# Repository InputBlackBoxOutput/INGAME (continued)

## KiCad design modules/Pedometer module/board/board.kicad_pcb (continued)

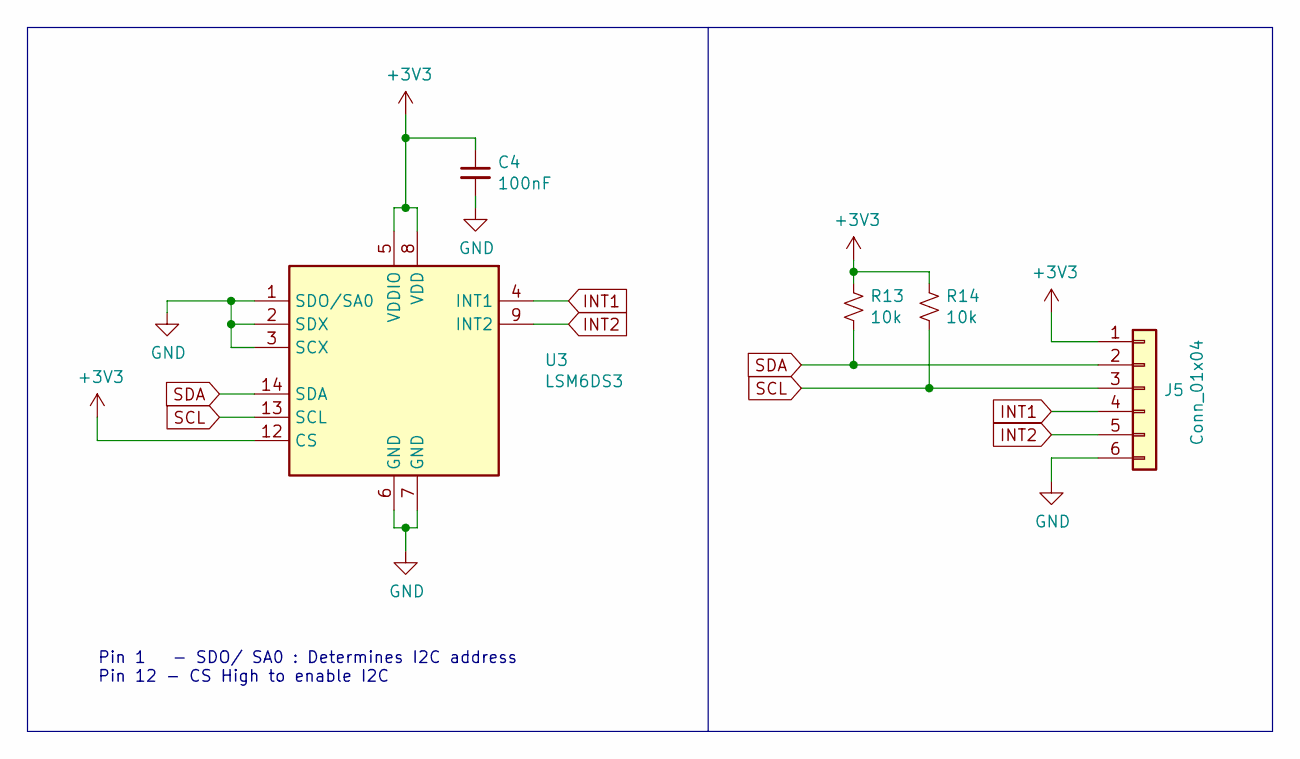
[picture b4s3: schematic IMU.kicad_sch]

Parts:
C4: 100nF; C_0603_1608Metric_Pad1.08x0.95mm_HandSolder
J5: Conn_01x04; SolderWire_1x06_P2.54mm
R13, R14: 10k; R_0603_1608Metric_Pad0.98x0.95mm_HandSolder
U3: LSM6DS3; LGA-14_3x2.5mm_P0.5mm_LayoutBorder3x4y

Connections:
GND: C4.2, J5.6, U3.1 (SDO/SA0), U3.2 (SDX), U3.3 (SCX), U3.6 (GND), U3.7 (GND); also elsewhere on the board
INT1: J5.4, U3.4 (INT1); also elsewhere on the board
INT2: J5.5, U3.9 (INT2); also elsewhere on the board
SCL: J5.3, R14.1, U3.13 (SCL); also elsewhere on the board
SDA: J5.2, R13.1, U3.14 (SDA); also elsewhere on the board

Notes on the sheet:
Pin 1 - SDO/ SA0 : Determines I2C address Pin 12 - CS High to enable I2C

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
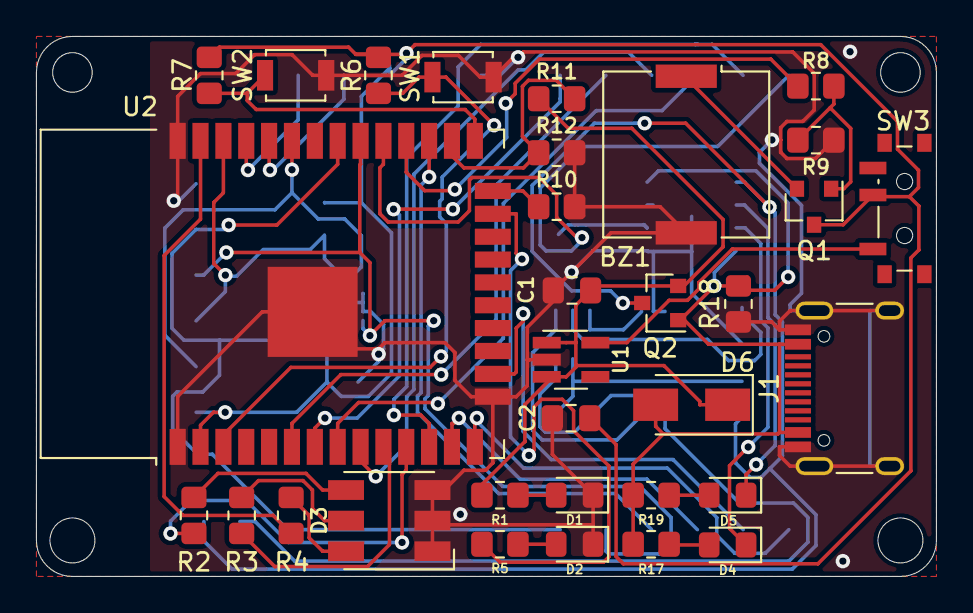
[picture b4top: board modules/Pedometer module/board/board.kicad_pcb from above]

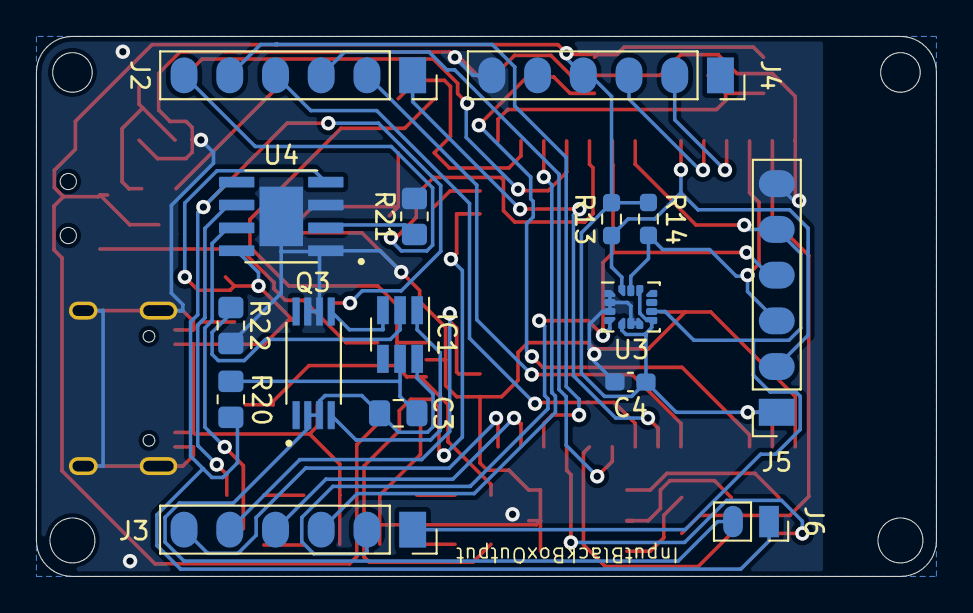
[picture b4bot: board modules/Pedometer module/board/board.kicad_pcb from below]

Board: 2 copper layers, 50.0 x 30.0 mm, 52 parts (16 on the bottom side), 48 nets.

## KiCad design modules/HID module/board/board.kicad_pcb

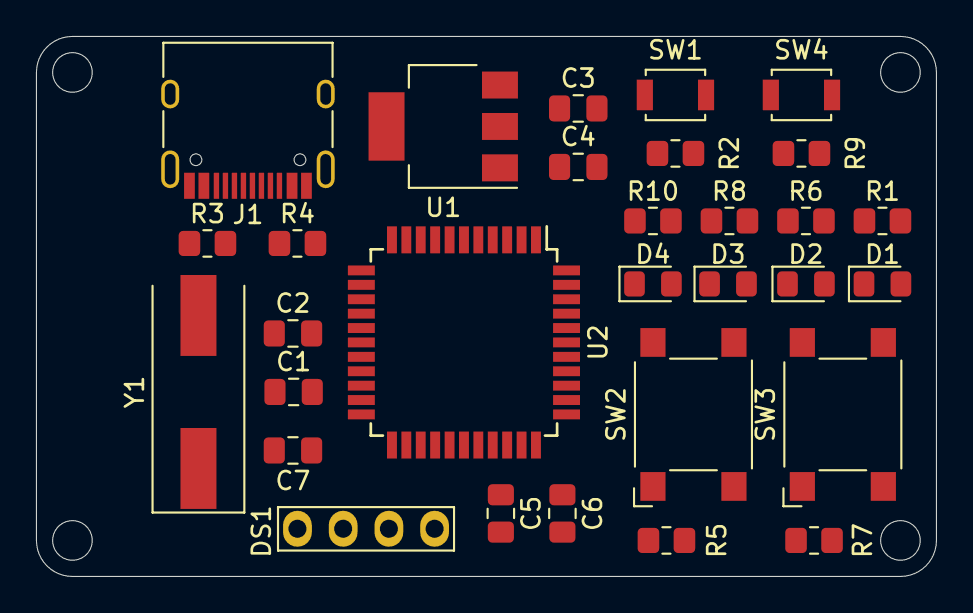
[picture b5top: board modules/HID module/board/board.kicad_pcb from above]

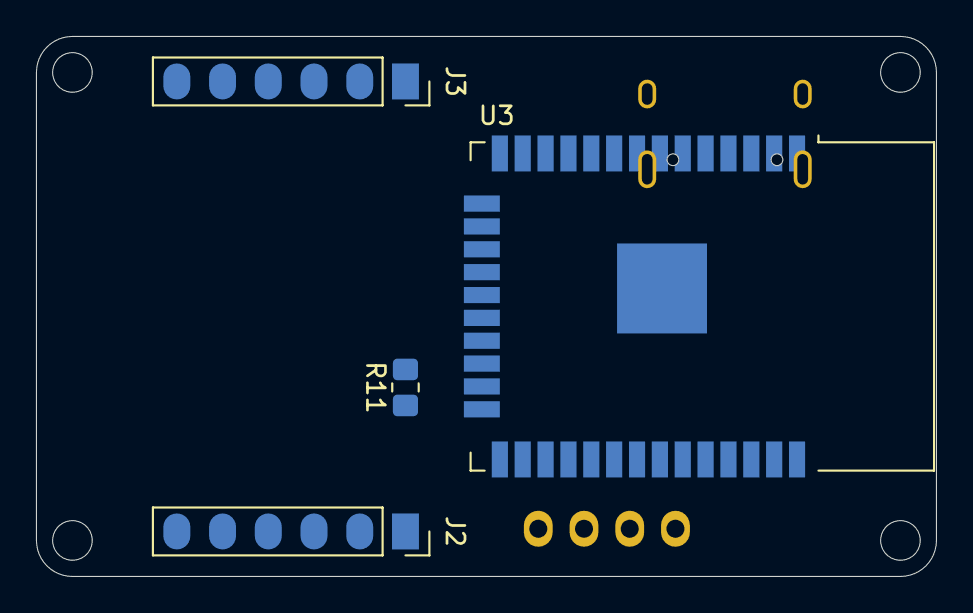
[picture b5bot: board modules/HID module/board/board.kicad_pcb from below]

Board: 2 copper layers, 50.0 x 30.0 mm, 38 parts (4 on the bottom side), 29 nets, no tracks yet.

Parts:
C1, C2: 22pF; C_0805_2012Metric_Pad1.18x1.45mm_HandSolder
C3: 10uF; C_0805_2012Metric_Pad1.18x1.45mm_HandSolder
C4: 22uF; C_0805_2012Metric_Pad1.18x1.45mm_HandSolder
C5, C7: 1uF; C_0805_2012Metric_Pad1.18x1.45mm_HandSolder
C6: 0.1uF; C_0805_2012Metric_Pad1.18x1.45mm_HandSolder
D1, D2, D3, D4: LED; LED_0805_2012Metric_Pad1.15x1.40mm_HandSolder
DS1: SSD1306; 128x64OLED
H1, H2, H3, H4: MountingHole; MountingHole_2.2mm_M2
J1: USB_C_Receptacle_USB2.0; USB_C_Receptacle_HRO_TYPE-C-31-M-12
J2, J3: Conn_01x06_Female; SolderWire_1x06_P2.54mm
R1, R2, R5, R6, R7, R8, R10: 10k; R_0805_2012Metric_Pad1.20x1.40mm_HandSolder
R3, R4: 22R; R_0805_2012Metric_Pad1.20x1.40mm_HandSolder
R9, R11: 5k; R_0805_2012Metric_Pad1.20x1.40mm_HandSolder
SW1, SW4: SW_Push; SW_SPST_B3U-1000P
SW2, SW3: SW_Push; SW_SPST_Omron_B3FS-100xP
U1: AMS1117-3.3; SOT-223-3_TabPin2
U2: ATmega32U4-AU; TQFP-44_10x10mm_P0.8mm
U3: ESP32-WROOM-32D; ESP32-WROOM-32
Y1: 16MHz; Crystal_SMD_HC49-SD

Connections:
+3V3: C4.1, J2.4, J3.4, R1.1, R2.1, R5.1, R7.1, R9.1, U1.2, U3.2
+5V: C3.1, C7.1, DS1.2, J1.A4, J1.A9, J1.B4, J1.B9, U1.3, U2.2, U2.7, U2.14, U2.24, U2.34, U2.44
/BTN-NEXT: R5.2, SW2.1, U2.28
/BTN-OK: R7.2, SW3.1, U2.29
/D+: R4.1, U2.4
/D-: R3.1, U2.3
/EN: R2.2, SW1.1, U2.13, U3.3
/IO2: R11.1, U3.24
/IO12: R10.1, U3.14
/IO14: R8.1, U3.13
/LED-K: R6.1, U2.27
/PD0: DS1.3, U2.18
/PD1: DS1.4, U2.19
/PD2: J2.2, U2.20
/PD3: J2.3, U2.21
/RX: J3.3, U3.34
/TX: J3.2, U3.35
/XTAL1: C1.1, U2.17, Y1.1
/XTAL2: C2.1, U2.16, Y1.2
GND: C1.2, C2.2, C3.2, C4.2, C5.2, C6.2, C7.2, D1.1, D2.1, D3.1, D4.1, DS1.1, J1.A1, J1.A12, J1.B1, J1.B12, J1.S1, J2.6, J3.6, R11.2, SW1.2, SW2.2, SW3.2, SW4.2, U1.1, U2.5, U2.15, U2.23, U2.33, U2.35, U2.43, U3.1, U3.15, U3.38, U3.39
unnamed: C5.1, U2.6
unnamed: C6.1, U2.42
unnamed: D1.2, R1.2
unnamed: D2.2, R6.2
unnamed: D3.2, R8.2
unnamed: D4.2, R10.2
unnamed: J1.A6, J1.B6, R4.2
unnamed: J1.A7, J1.B7, R3.2
unnamed: R9.2, SW4.1

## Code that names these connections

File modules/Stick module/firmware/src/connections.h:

#ifndef CONNECTIONS_H
#define CONNECTIONS_H

#define LED 13

#define BTN_21   4
#define BTN_22   5
#define BTN_23  12

#define BTN_11  14
#define BTN_12  15
#define BTN_13  16
#define BTN_14  17

#define AUX_1 23
#define AUX_2 25
#define AUX_3 26
#define AUX_4 27
#define AUX_5 32 // ADC
#define AUX_6 33 // ADC
#define AUX_7 34 // ADC
#define AUX_8 35 // ADC

#endif //CONNECTIONS_H

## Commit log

2021-12-07 Block diagrams added
2021-12-07 Datasheets, reference circuit images and character-set spreadsheet added
2021-12-09 HID module files added
2021-12-09 Controller module files added
2021-12-09 Pedometer module files added
2021-12-12 Enclosure files added
2021-12-12 Project overview file added
2022-02-20 Pedometer module: Schematic and PCB layout
2022-02-20 HID module: Schematic and PCB layout
2022-02-20 Controller module: Schematic and PCB layout
2022-03-09 Pedometer module: PCB size reduced
2022-03-13 Controller module: PCB complete
2022-03-13 HID module: PCB complete
2022-03-13 Pedometer module: PCB complete
2022-07-16 Controller module: PCB modular
2022-07-16 HID module: PCB modular
2022-07-16 Pedometer module: PCB modular
2022-09-17 README: System block diagram added
2022-11-26 File added: LICENSE
2022-12-06 README: Information added
2022-12-07 README: Minor changes
2022-12-27 ME6211 datasheet added
2023-01-31 Documents updated
2023-02-05 PCB: IMU
2023-02-05 PCB: USB receptacle moved closer to PCB edge
2023-02-08 Pedometer module: Firmware
2023-02-08 HID module: Firmware
2023-02-09 Controller module: Firmware
2023-02-09 Controller module: Button PCB
2023-02-10 HID module: Enclosure
2023-02-10 Pedometer module: Enclosure
2023-04-24 Controller module: Enclosure
2023-05-08 README: VR Headset
2023-05-19 Controller module: Optical Flow Sensor Connector
2023-06-25 HID enclosure options
2023-06-28 Pedometer enclosure options
2025-09-13 Add stick module
2025-09-13 Rescue connector symbols
